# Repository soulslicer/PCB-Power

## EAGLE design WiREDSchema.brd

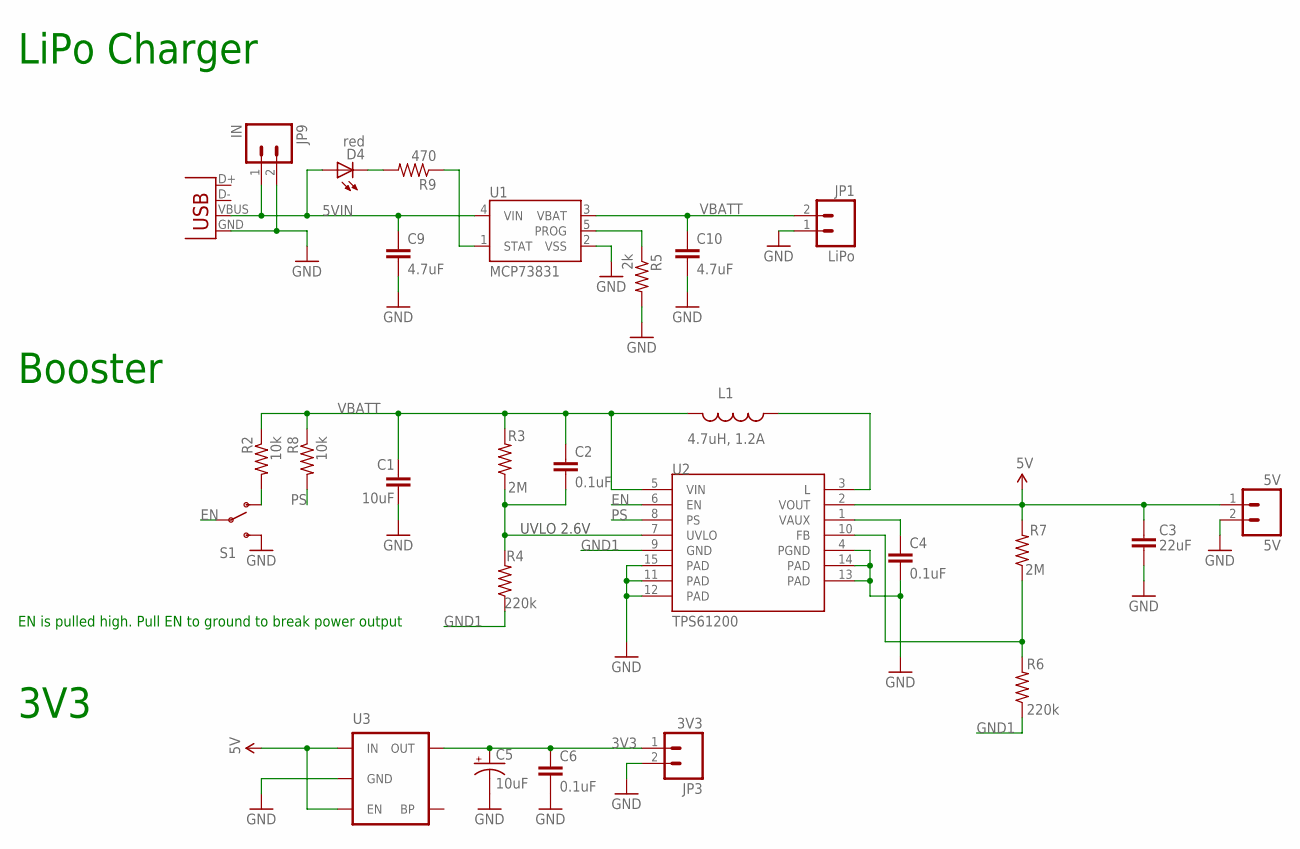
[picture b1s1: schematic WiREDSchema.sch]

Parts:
5V: 5V; 1X02
C1: 10uF; 1206; MPN 12066D106KAT2A
C2, C4, C6: 0.1uF; 0402-CAP; MPN 04026D104KAT2A
C3: 22uF; 0805; MPN C0805C226M9PACTU
C5: 10uF; EIA3216; MPN TAJA106K006RNJ
C9, C10: 4.7uF; 0402-CAP; MPN JMK105BBJ475MV-F
D4: red; LED-0603; MPN TLMS1100-GS08.
JP1: LiPo; JST-2-SMD
JP3: 3V3; 1X02
JP9: IN; 1X02
L1: 4.7uH, 1.2A; CDRH2D09; MPN SRR4011-4R7YL
R2, R8: 10k; 0402-RES; MPN CRG0402J10K
R3, R7: 2M; 0402-RES; MPN ERJ2GEJ205X
R4, R6: 220k; 0402-RES; MPN ERJ2GEJ224X
R5: 2k; 0402-RES; MPN ERJ2RKF2001X
R9: 470; 0402-RES; MPN CRG0402F470R
S1: SWITCH-SPDTSMD; AYZ0202
U1: MCP73831; SOT23-5; MPN MCP73831T-2ACI/OT
U2: TPS61200; QFN-10_PAD; MPN TPS61200DRCTG4
U3: MIC52053.3V; SOT23-5; MPN MIC5205YM5 TR
X1: USB-MICROB

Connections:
3V3: C5.A (+), C6.1, JP3.1, U3.5 (OUT)
5VIN: C9.1, D4.A, JP9.1, U1.4 (VIN), X1.VBUS
EN: S1.2, U2.6 (EN)
FB: R6.2, R7.1, U2.10 (FB)
GND: 5V.2, C1.2, C3.2, C4.2, C5.C (-), C6.2, C9.2, C10.2, JP1.1, JP3.2, JP9.2, R5.2, S1.3 (S), U1.2 (VSS), U2.4 (PGND), U2.11 (PAD), U2.12 (PAD), U2.13 (PAD), U2.14 (PAD), U2.15 (PAD), U3.2 (GND), X1.GND
GND1: R4.1, R6.1, U2.9 (GND)
unnamed: C4.1, U2.1 (VAUX)
unnamed: L1.P$1 (1), U2.3 (L)
unnamed: R2.2, S1.1 (O)
unnamed: D4.C, R9.2
unnamed: R5.1, U1.5 (PROG)
unnamed: R9.1, U1.1 (STAT)
PS: R8.2, U2.8 (PS)
UVLO: C2.2, R3.1, R4.2, U2.7 (UVLO)
VBATT: C1.1, C2.1, C10.1, JP1.2, L1.P$2 (2), R2.1, R3.2, R8.1, U1.3 (VBAT), U2.5 (VIN)
VCC: 5V.1, C3.1, R7.2, U2.2 (VOUT), U3.1 (IN), U3.3 (EN)

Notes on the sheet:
UVLO 2.6V
EN is pulled high. Pull EN to ground to break power output
LiPo Charger
Booster
3V3

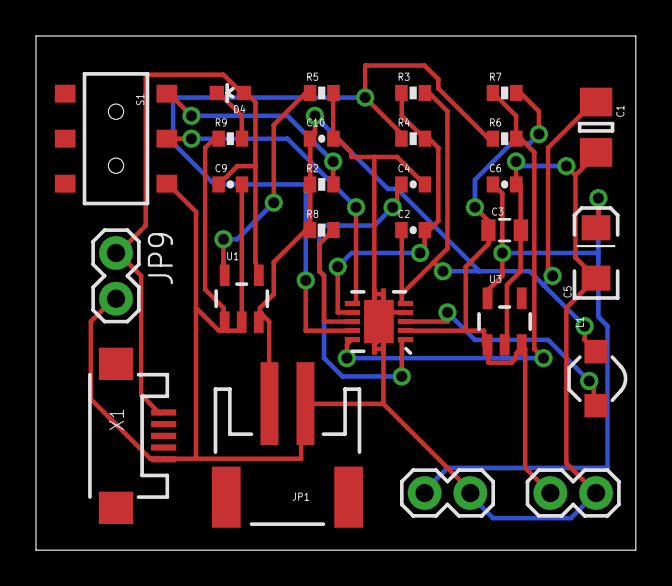
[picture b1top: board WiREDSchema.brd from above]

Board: 2 copper layers, 33.3 x 28.6 mm, 27 parts (0 on the bottom side), 16 nets.

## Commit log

2013-12-01 Gerber and shift down

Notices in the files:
parts and their libraries:
SparkFun-Electromechanical: Licensing: CC v3.0 Share-Alike You are welcome to use this library for commercial purposes.
